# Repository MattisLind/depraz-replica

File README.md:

# Depraz mouse replica

Based on the work by John Floren this project is aiming at creating a modern replica of the Depraz mouse. A mouse that outputs quadrature signals exactly as the original.

The physical 3D model will be the same as the Bellwether mouse by John but the circuit board is replaced. The new circuitboard is going to use an STM32F103 micro controller. Since this processor is using 3.3V IO no level shifters are necessary. On the board there will be a 3.3V LDO regulator and a 2.0V regulator, STM32F103 with 8MHz crystal and the PMW3389 mouse chip. The outputs from the STM32F103 to the host are using open drain to be able to handle 5V outputs. 

# Old Bellwether project

This repo should contain everything you need to make a [Bellwether mouse](https://jfloren.net/bellwether.html).

Note that I've made several of these myself, but it's possible that I've forgotten a step or component somewhere.

I'm willing to answer questions to the best of my ability. I'll also consider assembling some portions of the mouse and mailing it out; send me an email if you want this.

The 3d models and the circuit are CC BY-NC-SA licensed. I believe this means that "group buys" (where 1 person coordinates ordering a bunch of PCBs and parts) are ok under this model.

## 3D-printed case

Inside the case/ subdirectory you'll find two FreeCAD files, "base" (the bottom part of the mouse) and "body" (the curved top which fits in your hand).

These should be printed in PLA. I've had good luck with my Prusa Mini. I strongly suggest using a raft when printing the body, and *not* using a raft for the base.

Check out the releases for pre-built STL files.

## PCB

The board was designed using KiCAD. If you use OSH Park, you should be able to just upload board/depraz_board.kicad_pcb directly on their site. For other PCB services, you may need to open KiCAD and export Gerber files etc.

## Circuit & BOM

You can check out the schematic in schematic.pdf

bom.csv is a circuit bill of materials. Most stuff should be available from parts companies in the US, but for the PMW3389 sensor you'll probably need to go to AliExpress (e.g. https://www.aliexpress.us/item/2251832705021246.html)

You'll also need 3 momentary pushbutton switches such as https://www.digikey.com/en/products/detail/5501M1BLKX/EG1701-ND/101654

Although you don't have to, I recommend using a DIP socket for the microcontroller in case you toast the microcontroller.

## Assembly

### Circuit assembly

In general it's all pretty straightforward but I strongly recommend installing the SMD level shifters first, all the rest of the components next, and then do the mouse sensor *last*.

### Doing the switches

I recommend gluing down the switches first. Gently pry off the button from each switch and set it aside. Then put a small dab of Gorilla Glue in the slot on the base, press the switch onto it, and make sure it's aligned straight. Use a clamp to hold the switch in place while the glue dries (I used something like https://www.amazon.com/Professional-Plastic-Backdrop-Photography-Improvement/dp/B08RXW32H4/). Once the glue is dry, make sure the switch is firmly seated and use an exacto knife to trim away any glue which oozed out, then press the button back onto the switch face.

Solder two wires onto each switch, on the normally-open pins. The wires should have Dupont pin connectors on the ends; I just took some jumper wires I had lying around (with a connector on each end) and cut them in half. See http://jfloren.net/content/bellwether/base2.jpg

### Physical assembly

You'll need the following parts to assemble the case:

* 8x M2x0.4mm heatserts: https://www.mcmaster.com/94459A120/
* 4x M2x0.4mm flathead screws (for the bottom): https://www.mcmaster.com/91294A003/
* 4x M2x0.4mm button head screws (to hold the board down): https://www.mcmaster.com/92095A451/

Additional stuff you'll want:

* A USB cable. Should be USB-A on one end, and a female pin header connector at the other. You can start with https://www.digikey.com/en/products/detail/assmann-wsw-components/A-USB20AM-OE-200BK28/10408422 and use https://www.amazon.com/Taiss-Ratcheting-Connector-Crimping-Terminal/dp/B0B11RLGDZ to crimp on a 4-pin header to the other end. You may be able to find these pre-made, e.g. https://www.amazon.com/dp/B07ZPT2NMT
* Friction tape (https://www.amazon.com/gp/product/B0000CBIAT) to wrap around the USB cable where it leaves the mouse. This appears to be what my original Depraz mouse used.
* Teflon tape to make skates for the bottom. I used https://www.amazon.com/gp/product/B01LZ44P6M and punched out pieces using https://www.amazon.com/gp/product/B00006IBK9

Use your soldering iron to install the heatserts flush in the corresponding holes of the case.

Position the lens on the bottom of the mouse sensor, then set the PCB on the 3d printed base. Use the button-head screws to hold down the PCB; don't overtighten!

Plug in the switches. Note that the headers on the board are labeled R, M, and L for right, middle, and left.

Plug the USB cable into the 4-pin USB header. Lay it across the board to where the cable hole in the case will go; mark this point and put a layer or two of friction tape on the cable there.

Gently slide the top of the case over the switches; there's a "right way" to do it, which takes a bit of gentle experimentation to find. Once you get the two pieces together, use flathead screws to hold them together.

Punch out four pieces of Teflon tape and stick them to the bottom for skates.

### Flashing the firmware

The firmware organization sucks, but I am not good enough at PIC programming to properly clean it up. PRs welcome.

Plug your PIC programmer into the PROGRAM header on the board.

Open MPLAB X IDE and load firmware/depraz/apps/usb/device/hid_mouse/firmware/low_pin_count_usb_development_kit_pic16f1459.x

I found that it worked when I set up the PICkit3 to provide power at 3.5V. Your other option is to plug in the USB cable before programming to power the device externally.

### Adding heft

You'll probably find that the mouse by itself is way too light. I hot-glued a bunch of lead fishing weights to the inside and it was much more pleasant.

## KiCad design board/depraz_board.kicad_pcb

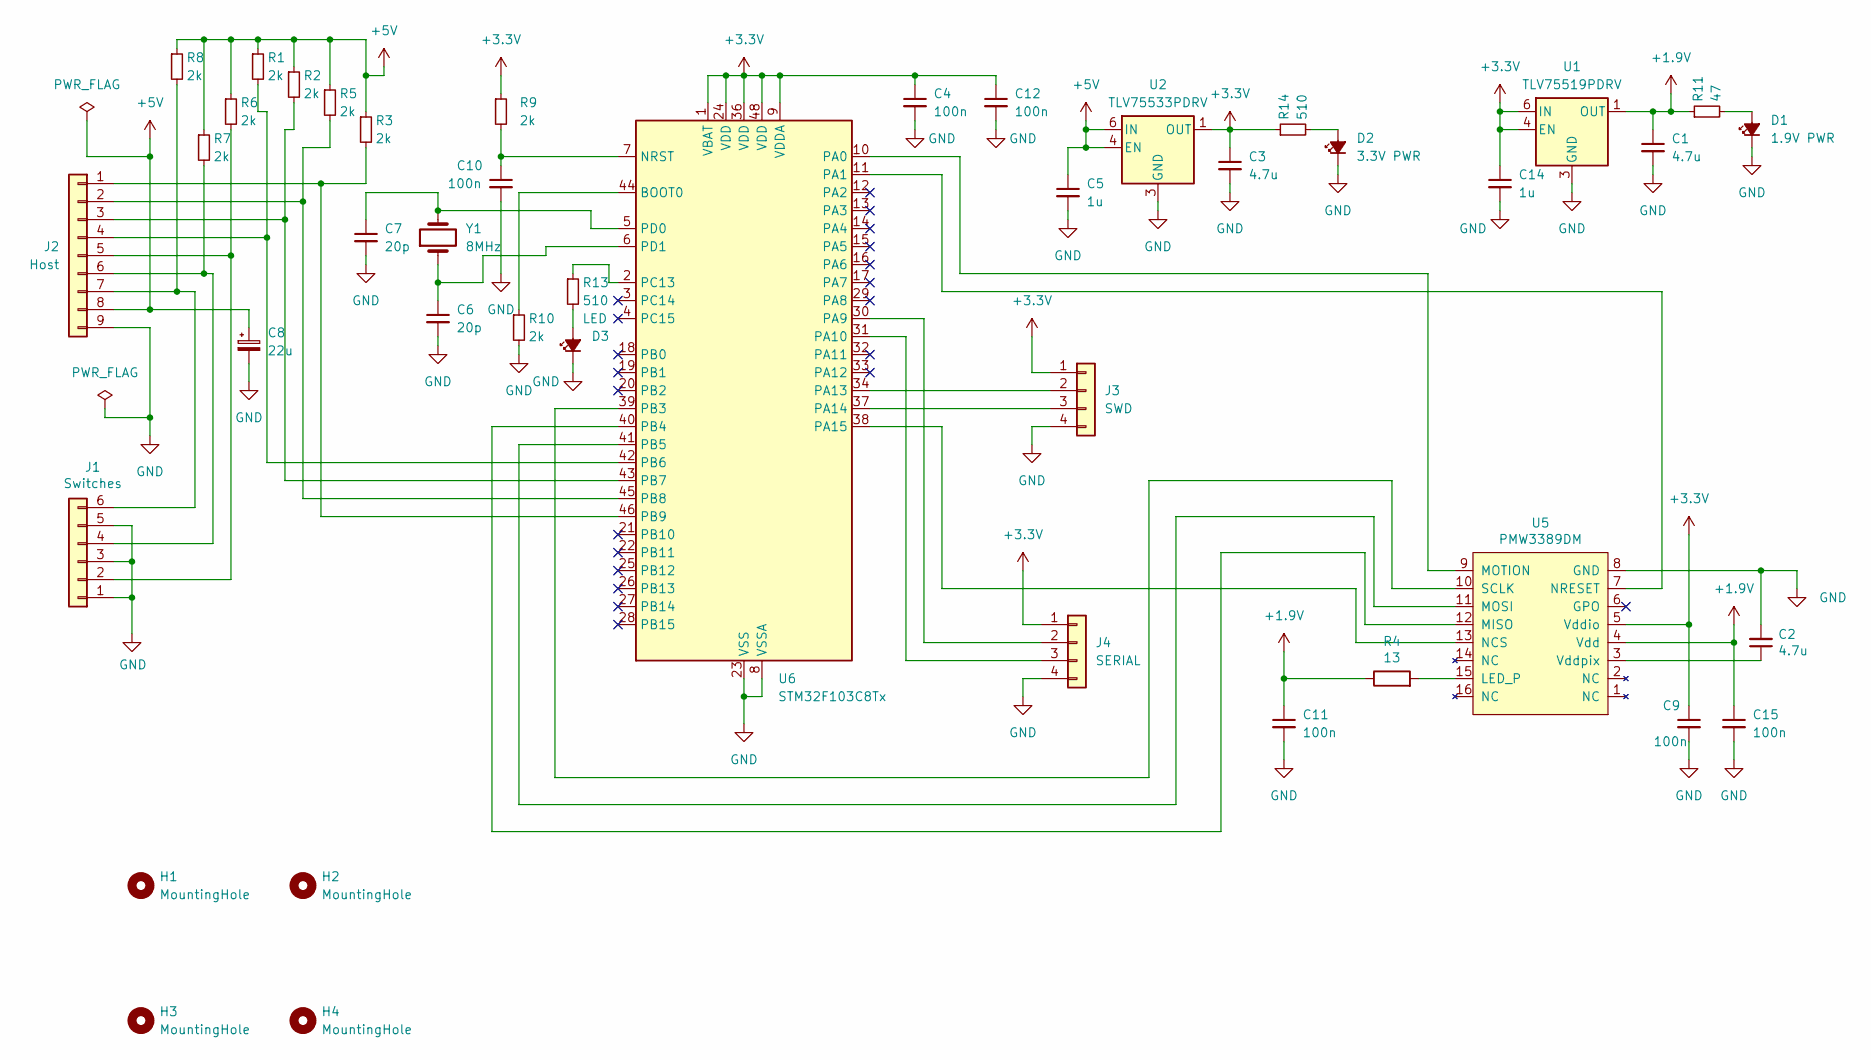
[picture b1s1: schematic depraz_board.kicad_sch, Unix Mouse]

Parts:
C1, C2, C3: 4.7u; C_1206_3216Metric; LCSC C29823
C4, C9, C10, C11, C12, C15: 100n; C_0402_1005Metric; LCSC C1525
C5, C14: 1u; C_0805_2012Metric; LCSC C28323
C6, C7: 20p; C_0402_1005Metric; LCSC C1554
C8: 22u; CP_Elec_4x5.4; LCSC C3356
D1: 1.9V PWR; LED_0603_1608Metric; LCSC C2286
D2: 3.3V PWR; LED_0805_2012Metric; LCSC C2297
D3: LED; LED_0805_2012Metric; LCSC C2296
H1, H2, H3, H4: MountingHole; MountingHole_2.7mm_M2.5
J1: Switches; PinHeader_1x06_P2.54mm_Vertical
J2: Host; PinHeader_1x09_P2.54mm_Vertical
J3: SWD; PinHeader_1x04_P2.54mm_Vertical
J4: SERIAL; PinHeader_1x04_P2.54mm_Vertical
R1, R2, R3, R5, R6, R7, R8, R9, R10: 2k; R_0402_1005Metric; LCSC C4109
R4: 13; R_0805_2012Metric; LCSC C25282
R11: 47; R_0603_1608Metric; LCSC C23182
R13, R14: 510; R_0402_1005Metric; LCSC C25123
U1: TLV75519PDRV; WSON-6-1EP_2x2mm_P0.65mm_EP1x1.6mm; LCSC C2861631
U2: TLV75533PDRV; WSON-6-1EP_2x2mm_P0.65mm_EP1x1.6mm; LCSC C2861750
U5: PMW3389DM; pmw3389
U6: STM32F103C8Tx; LQFP-48_7x7mm_P0.5mm; LCSC C8734
Y1: 8MHz; Crystal_SMD_HC49-SD; LCSC C20617538

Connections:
+1.9V: C1.1, C11.1, C15.1, R4.1, R11.1, U1.1 (OUT), U5.4 (Vdd)
+3.3V: C3.1, C4.1, C9.1, C12.1, C14.1, J3.1, J4.1, R9.1, R14.1, U1.4 (EN), U1.6 (IN), U2.1 (OUT), U5.5 (Vddio), U6.1 (VBAT), U6.9 (VDDA), U6.24 (VDD), U6.36 (VDD), U6.48 (VDD)
+5V: C5.1, C8.1, J2.8, R1.1, R2.1, R3.1, R5.1, R6.1, R7.1, R8.1, U2.4 (EN), U2.6 (IN)
GND: C1.2, C2.2, C3.2, C4.2, C5.2, C6.2, C7.2, C8.2, C9.2, C10.2, C11.2, C12.2, C14.2, C15.2, D1.1 (K), D2.1 (K), D3.1 (K), J1.1, J1.3, J1.5, J2.9, J3.4, J4.4, R10.2, U1.3 (GND), U1.7 (GND), U2.3 (GND), U2.7 (GND), U5.8 (GND), U6.8 (VSSA), U6.23 (VSS), U6.35 (VSS), U6.47 (VSS)
unnamed: D1.2 (A), R11.2
unnamed: D2.2 (A), R14.2
unnamed: D3.2 (A), R13.2
unnamed: J1.2, J2.5, R6.2
unnamed: J1.4, J2.6, R7.2
unnamed: J1.6, J2.7, R8.2
unnamed: J2.1, R3.2, U6.46 (PB9)
unnamed: J2.2, R5.2, U6.45 (PB8)
unnamed: J2.3, R2.2, U6.43 (PB7)
unnamed: J2.4, R1.2, U6.42 (PB6)
unnamed: J3.2, U6.34 (PA13)
unnamed: J3.3, U6.37 (PA14)
unnamed: J4.2, U6.30 (PA9)
unnamed: J4.3, U6.31 (PA10)
unnamed: R4.2, U5.15 (LED_P)
unnamed: U5.12 (MISO), U6.40 (PB4)
unnamed: U5.11 (MOSI), U6.41 (PB5)
unnamed: U5.9 (MOTION), U6.10 (PA0)
unnamed: U5.13 (NCS), U6.38 (PA15)
unnamed: U5.7 (NRESET), U6.11 (PA1)
unnamed: U5.10 (SCLK), U6.39 (PB3)
unnamed: C2.1, U5.3 (Vddpix)
unnamed: R10.1, U6.44 (BOOT0)
unnamed: C10.1, R9.2, U6.7 (NRST)
unnamed: R13.1, U6.2 (PC13)
unnamed: C7.1, U6.5 (PD0), Y1.2
unnamed: C6.1, U6.6 (PD1), Y1.1

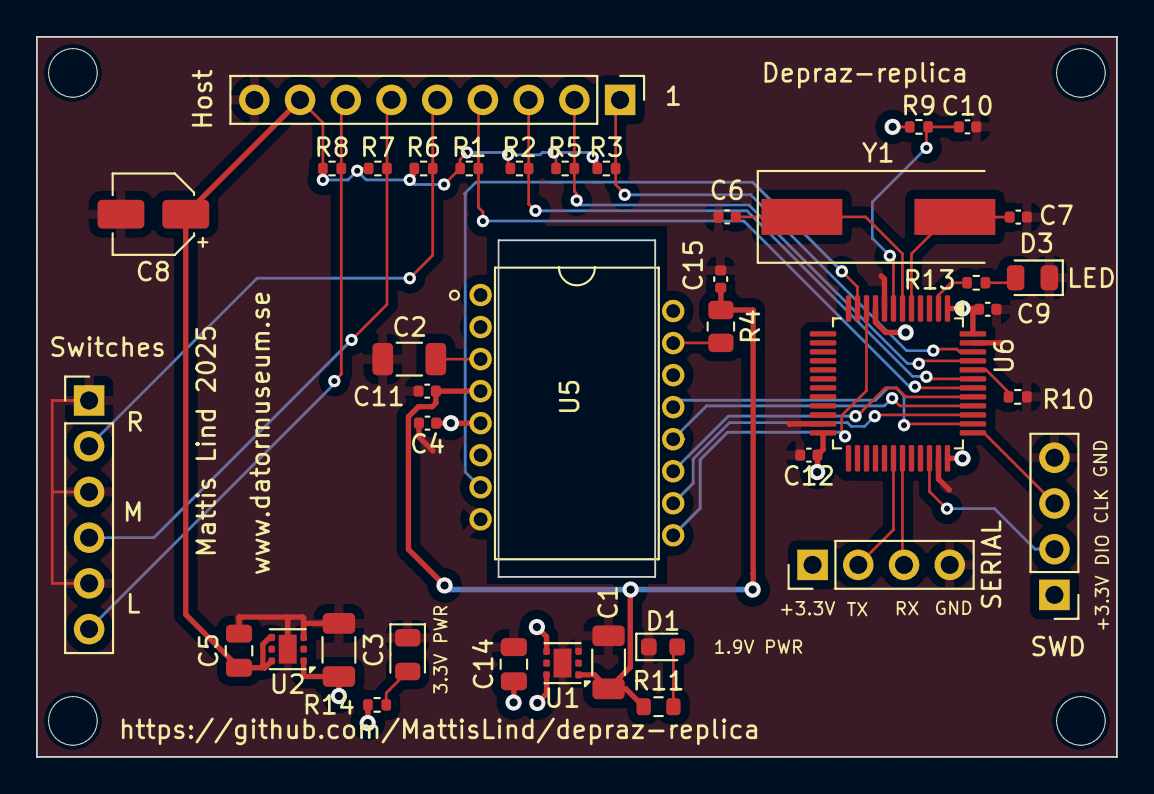
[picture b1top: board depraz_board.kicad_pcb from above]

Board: 2 copper layers, 60.0 x 40.0 mm, 43 parts (0 on the bottom side), 31 nets.

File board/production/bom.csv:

Designator,Footprint,Quantity,Value,LCSC Part #
"C1, C2, C3",1206,3,4.7u,C29823
"C10, C11, C12, C15, C4, C9",0402,6,100n,C1525
"C14, C5",0805,2,1u,C28323
"C6, C7",0402,2,20p,C1554
C8,CP_Elec_4x5.4,1,22u,C3356
D1,0603,1,1.9V PWR,C2286
D2,0805,1,3.3V PWR,C2297
D3,0805,1,LED,C2296
J1,PinHeader_1x06_P2.54mm_Vertical,1,Switches,
J2,PinHeader_1x09_P2.54mm_Vertical,1,Host,
J3,PinHeader_1x04_P2.54mm_Vertical,1,SWD,
J4,PinHeader_1x04_P2.54mm_Vertical,1,SERIAL,
"R1, R10, R2, R3, R5, R6, R7, R8, R9",0402,9,2k,C4109
R11,0603,1,47,C23182
"R13, R14",0402,2,510,C25123
R4,0805,1,13,C25282
U1,WSON-6-1EP_2x2mm_P0.65mm_EP1x1.6mm,1,TLV75519PDRV,C2861631
U2,WSON-6-1EP_2x2mm_P0.65mm_EP1x1.6mm,1,TLV75533PDRV,C2861750
U5,pmw3389,1,PMW3389DM,
U6,LQFP-48_7x7mm_P0.5mm,1,STM32F103C8Tx,C8734
Y1,Crystal_SMD_HC49-SD,1,8MHz,C20617538

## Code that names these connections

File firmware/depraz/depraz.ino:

/*

  First attempt as created by ChatGPT. Interesting to see how this works. If it even compile...

  PMW3389 → Quadrature bridge (init aligned with depraz demo main.c)

  Init flow (like your demo):
    1) Read ProductID
    2) Read Motion + DeltaX/DeltaY (clear state)
    3) Write resolution (CPI) to CONFIG1
    4) Write Motion register (value configurable below)
    5) Enter loop reading deltas

  Hardware (STM32, Arduino_Core_STM32):
    - SPI1: PB3=SCK, PB4=MISO, PB5=MOSI; NCS=PA15
    - MOTION=PA0 (input), NRESET=PA1 (output)
    - Quadrature out: X1=PB6, X2=PB7, Y1=PB8, Y2=PB9
    - LED: PC13 (active-low on many boards)
    - Debug UART: USART1 on PA9/PA10 (define DEBUG_SERIAL 1 to enable)
    - JTAG disabled, SWD kept enabled

  NOTE: Many PMW33xx designs require SROM upload after reset for valid motion.
        Your demo’s simple init works on your board/firmware; we follow that here.
*/

#include <SPI.h>

// ------------------------- Compile-time configuration ------------------

// Enable/disable serial debug (USART1 PA9/PA10)
#define DEBUG_SERIAL 1

// Desired resolution in CPI; PMW3389 uses 50-CPI steps via CONFIG1
#define DESIRED_CPI 1600

// Value to write to MOTION register in init step (match your demo).
// If your original code used another value, change here.
#define MOTION_WRITE_VAL 0x00

// Quadrature pulse width per half-step (µs)
#define QUAD_PULSE_US 20

// Sample rate 100 Hz = 10 ms
#define SAMPLE_PERIOD_MS 10

// ------------------------- Pin assignments -----------------------------

const uint8_t PIN_NCS    = PA15; // PMW3389 NCS
const uint8_t PIN_MOTION = PA0;  // PMW3389 MOTION (interrupt)
const uint8_t PIN_NRESET = PA1;  // PMW3389 NRESET (output)

const uint8_t PIN_X1 = PB6; // Quadrature X A
const uint8_t PIN_X2 = PB7; // Quadrature X B
const uint8_t PIN_Y1 = PB8; // Quadrature Y A
const uint8_t PIN_Y2 = PB9; // Quadrature Y B

const uint8_t PIN_LED = PC13;

// ------------------------- PMW3389 register map (subset) ---------------

// Common PMW33xx regs; names per datasheet family
#define REG_PRODUCT_ID     0x00
#define REG_REVISION_ID    0x01
#define REG_MOTION         0x02
#define REG_DELTA_X_L      0x03
#define REG_DELTA_X_H      0x04
#define REG_DELTA_Y_L      0x05
#define REG_DELTA_Y_H      0x06
#define REG_CONFIG1        0x0F  // CPI = value*50 (range 1..0xFF depending on model)

// ------------------------- Globals/state --------------------------------

volatile bool motionFlag = false;     // set in MOTION ISR
uint8_t quadStateX = 0;               // 2-bit Gray state
uint8_t quadStateY = 0;
uint32_t lastSampleMs = 0;

// ------------------------- HAL: disable JTAG, keep SWD ------------------


static void disableJTAG_keepSWD() {
  // Frigör PB3/PB4/PB5 för SPI men behåll SWD för debug/programmering
  __HAL_AFIO_REMAP_SWJ_NOJTAG();
}

// ------------------------- LED helpers ----------------------------------

inline void ledOn() {
  digitalWrite(PIN_LED, HIGH);
}

inline void ledOff() {
  digitalWrite(PIN_LED, LOW);
}

// ------------------------- SPI helpers ----------------------------------

inline void ncsLow()  { digitalWrite(PIN_NCS, LOW);  }
inline void ncsHigh() { digitalWrite(PIN_NCS, HIGH); }

// PMW3389 uses SPI mode 3
static uint8_t spiReadReg(uint8_t reg) {
  SPI.transfer(reg & 0x7F);          // MSB=0 for read
  delayMicroseconds(1);              // tSRAD (säker marginal)
  uint8_t v = SPI.transfer(0x00);
  delayMicroseconds(10);
  return v;
}

static void spiWriteReg(uint8_t reg, uint8_t val) {
  SPI.transfer(reg | 0x80);          // MSB=1 for write
  SPI.transfer(val);
  delayMicroseconds(10);             
}

// ------------------------- Sensor init (matches your demo) --------------

static void sensorInitSimple() {
  // (Valfri) hårdvarureset via NRESET om kopplad
  digitalWrite(PIN_NRESET, LOW);
  delay(100);
  digitalWrite(PIN_NRESET, HIGH);
  delay(1000);

  uint8_t pid = spiReadReg(REG_PRODUCT_ID);
  uint8_t rev = spiReadReg(REG_REVISION_ID);
#if DEBUG_SERIAL
  Serial1.print("ProductID=0x"); Serial1.print(pid, HEX);
  Serial1.print(" RevisionID=0x"); Serial1.println(rev, HEX);
#endif

  (void)spiReadReg(REG_MOTION);
  (void)spiReadReg(REG_DELTA_X_L);
  (void)spiReadReg(REG_DELTA_X_H);
  (void)spiReadReg(REG_DELTA_Y_L);
  (void)spiReadReg(REG_DELTA_Y_H);

  uint8_t cpi_val = (uint8_t)((DESIRED_CPI + 49) / 50);
  spiWriteReg(REG_CONFIG1, cpi_val);
#if DEBUG_SERIAL
  Serial1.print("CPI set to "); Serial1.print((int)cpi_val * 50);
  Serial1.print(" (CONFIG1=0x"); Serial1.print(cpi_val, HEX); Serial1.println(")");
#endif

  spiWriteReg(REG_MOTION, MOTION_WRITE_VAL);
#if DEBUG_SERIAL
  Serial1.print("Motion reg written: 0x");
  Serial1.println(MOTION_WRITE_VAL, HEX);
#endif
}


// ------------------------- Quadrature generation ------------------------

static const uint8_t graySeq[4] = { 0b00, 0b01, 0b11, 0b10 };

inline void writeXPins(uint8_t bits) {
  digitalWrite(PIN_X1, (bits & 0x01) ? HIGH : LOW); // A
  digitalWrite(PIN_X2, (bits & 0x02) ? HIGH : LOW); // B
#if DEBUG_SERIAL
  Serial1.print("X1:");
  Serial1.println(bits & 0x01, DEC);
  Serial1.print("X2:");
  Serial1.println((bits>>1) & 0x01, DEC);
#endif

}

inline void writeYPins(uint8_t bits) {
  digitalWrite(PIN_Y1, (bits & 0x01) ? HIGH : LOW); // A
  digitalWrite(PIN_Y2, (bits & 0x02) ? HIGH : LOW); // B
#if DEBUG_SERIAL
  Serial1.print("Y1:");
  Serial1.println(bits & 0x01, DEC);
  Serial1.print("Y2:");
  Serial1.println(((bits>>1) & 0x01), DEC);
#endif  
}

static void stepQuadX(int steps) {
  int n = steps;
  int dir = (n >= 0) ? +1 : -1;
  n = abs(n);
  while (n--) {
    quadStateX = (quadStateX + (dir > 0 ? 1 : 3)) & 0x03;
    writeXPins(graySeq[quadStateX]);
    delayMicroseconds(QUAD_PULSE_US);
  }
}

static void stepQuadY(int steps) {
  int n = steps;
  int dir = (n >= 0) ? +1 : -1;
  n = abs(n);
  while (n--) {
    quadStateY = (quadStateY + (dir > 0 ? 1 : 3)) & 0x03;
    writeYPins(graySeq[quadStateY]);
    delayMicroseconds(QUAD_PULSE_US);
  }
}

// ------------------------- Read deltas at 100 Hz ------------------------

static void readDeltas(int16_t &dx, int16_t &dy) {
  uint8_t motion = spiReadReg(REG_MOTION);
  uint8_t xl = spiReadReg(REG_DELTA_X_L);
  uint8_t xh = spiReadReg(REG_DELTA_X_H);
  uint8_t yl = spiReadReg(REG_DELTA_Y_L);
  uint8_t yh = spiReadReg(REG_DELTA_Y_H);

  dx = (int16_t)(((int16_t)xh << 8) | xl);
  dy = (int16_t)(((int16_t)yh << 8) | yl);

#if DEBUG_SERIAL
  // Enkel spårning av MOTION-bit för diagnos
  //Serial1.print("MOTION=0x"); Serial1.print(motion, HEX);
  //Serial1.print(" dx="); Serial1.print(dx);
  //Serial1.print(" dy="); Serial1.println(dy);
#endif
}

// ------------------------- Setup / Loop ---------------------------------

void setup() {
  disableJTAG_keepSWD();

  // LED
  pinMode(PIN_LED, OUTPUT);
  ledOff();

  // Quadrature outputs are open drain
  pinMode(PIN_X1, OUTPUT_OPEN_DRAIN);
  pinMode(PIN_X2, OUTPUT_OPEN_DRAIN);
  pinMode(PIN_Y1, OUTPUT_OPEN_DRAIN);
  pinMode(PIN_Y2, OUTPUT_OPEN_DRAIN);
  writeXPins(graySeq[quadStateX]);
  writeYPins(graySeq[quadStateY]);

  pinMode(PIN_NCS, OUTPUT);   ncsHigh();
  pinMode(PIN_NRESET, OUTPUT); digitalWrite(PIN_NRESET, HIGH);


#if DEBUG_SERIAL
  Serial1.begin(115200);
  delay(10);
  Serial1.println("\nPMW3389 → Quadrature");
#endif

  SPI.setMISO(PB4);
  SPI.setMOSI(PB5);
  SPI.setSCLK(PB3);
  SPI.setSSEL(PA15);
  SPI.begin();
  SPI.beginTransaction(SPISettings(2000000, MSBFIRST, SPI_MODE3));
  sensorInitSimple();

  lastSampleMs = millis();
}

void loop() {
  uint32_t now = millis();

  if ((uint32_t)(now - lastSampleMs) >= SAMPLE_PERIOD_MS) {
    lastSampleMs += SAMPLE_PERIOD_MS;

    int16_t dx = 0, dy = 0;
    readDeltas(dx, dy);

    if (dx != 0 || dy != 0) {
      ledOn();
      stepQuadX(dx); 
      stepQuadY(dy);
      ledOff();
    } 

  }

  delay(1);
}

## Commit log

2025-08-23 New layout for a STM32 based Depraz replica with quadrature outputs.
2025-08-23 Updated schematic.
2025-08-23 Added LCSC part numbers for the SMD parts.
2025-08-24 Fixes after review.
2025-08-24 Fixed PCB
2025-08-25 Fixed layout after review.
2025-09-03 Update depraz.ino
    Updated with simple init code
2025-09-20 Delete files
    Delete old stuff
2025-09-21 Update depraz.ino
    We use the New Arduino_STM32_Core instead of maple since it is getting old.
2025-09-21 Fixed SPI pin routing
    Compiles and seems to actually do something useful. The SPI pins was not routed correctly.
2025-09-21 Update depraz.ino
    Some debugging and other changes. Seems to work. Need real testing now
2025-09-21 Update depraz.ino
    Clean up
2025-09-21 Added JLCPCB production files.
